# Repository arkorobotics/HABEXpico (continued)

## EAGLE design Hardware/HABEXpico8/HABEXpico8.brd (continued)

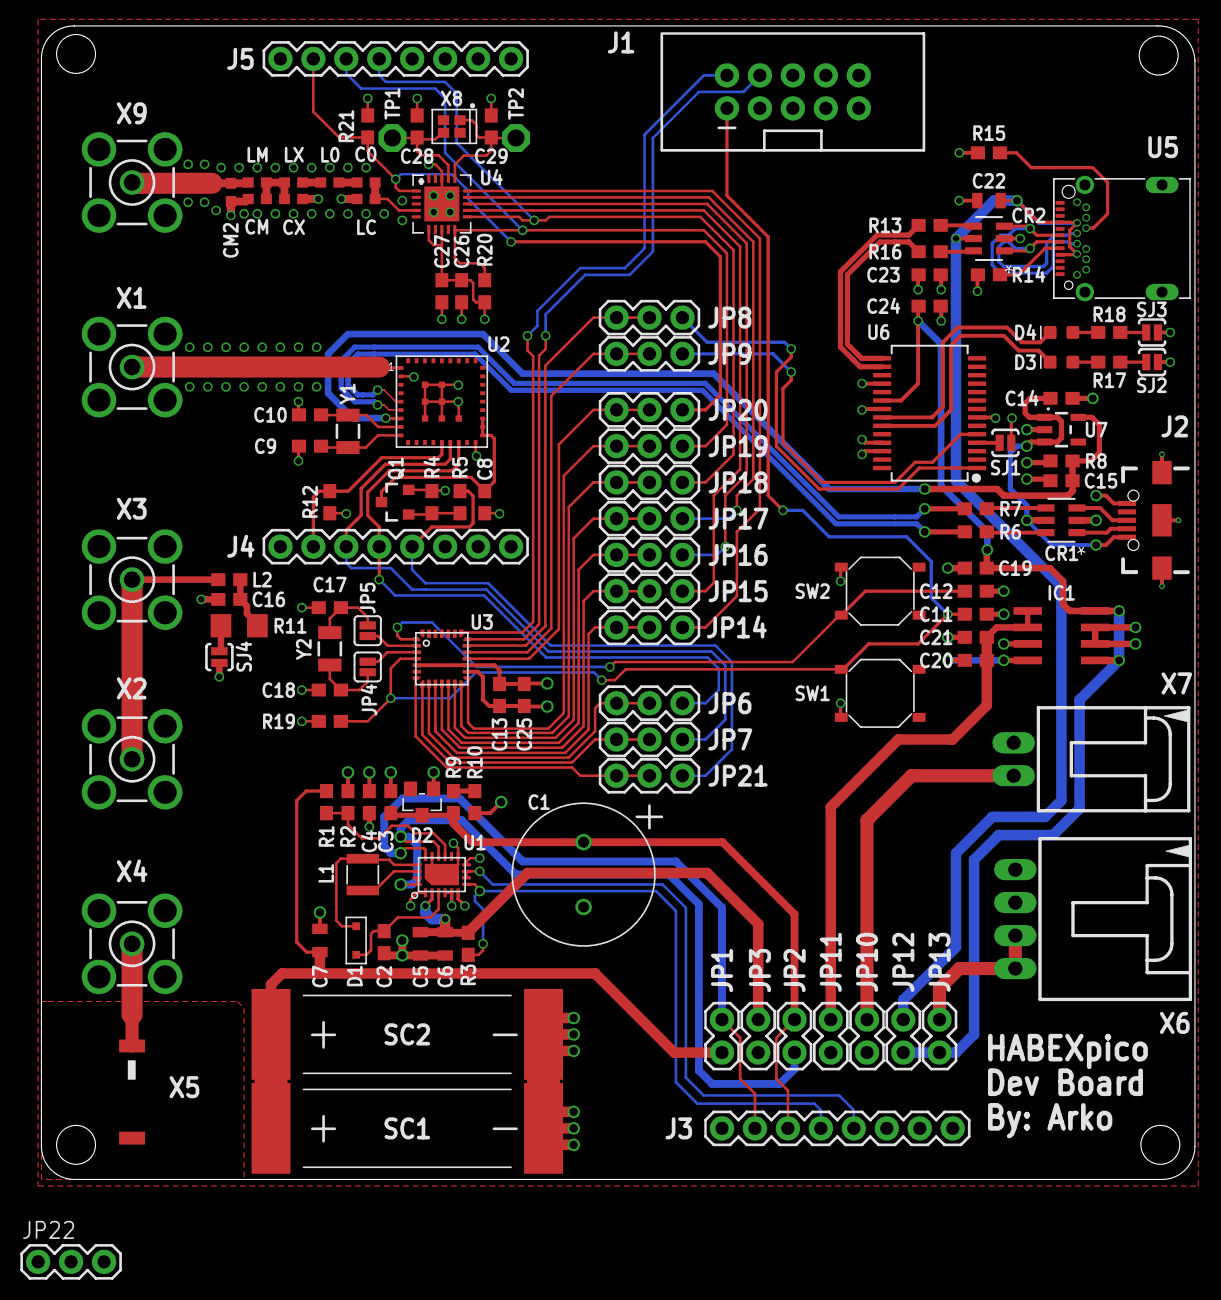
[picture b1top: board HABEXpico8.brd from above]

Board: 4 copper layers, 88.9 x 88.9 mm, 123 parts (0 on the bottom side), 93 nets.

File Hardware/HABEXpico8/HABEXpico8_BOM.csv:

"Qty";"Value";"Device";"Package";"Parts";"Description";"MANUFACTURER_PART_NUMBER";"MF";"MFG_PN";"MPN";"OC_FARNELL";"OC_NEWARK";"PROD_ID";"SF_ID";"SPICEPREFIX";"TP_SIGNAL_NAME";"VALUE";"VENDOR";
"5";"";"BU-SMA-V";"BU-SMA-V";"X1, X2, X3, X4, X9";"FEMALE SMA CONNECTOR";"";"";"";"";"unknown";"unknown";"";"";"";"";"";"";
"1";"";"CONN_05X2SHD";"2X5-SHROUDED";"J1";"Multi connection point. Often used as Generic Header-pin footprint for 0.1 inch spaced/style header connections";"";"";"";"";"";"";"CONN-08671";"PRT-08506";"";"";"";"";
"3";"";"CONN_08"";"1X08";"J3, J4, J5";"Multi connection point. Often used as Generic Header-pin footprint for 0.1 inch spaced/style header connections";"";"";"";"";"";"";"CONN-08438";"";"";"";"";"";
"7";"";"JUMPER-2PTH";"1X02";"JP1, JP2, JP3, JP10, JP11, JP12, JP13";"Jumper";"";"";"";"";"";"";"";"";"";"";"";"";
"12";"";"JUMPER-3PTH";"1X03";"JP6, JP7, JP8, JP9, JP14, JP15, JP16, JP17, JP18, JP19, JP20, JP21";"";"";"";"";"";"";"";"";"";"";"";"";"";
"2";"";"JUMPER-SMT_2_NO_SILK";"SMT-JUMPER_2_NO_SILK";"JP4, JP5";"Normally open jumper";"";"";"";"";"";"";"";"";"";"";"";"";
"1";"";"LT1763CS8-3.3";"SOIC8";"IC1";"500mA, Low Noise, LDO Micropower Regulators";"";"";"";"LT1763CS8-3.3";"1273617";"57M6055";"";"";"";"";"";"";
"1";"";"SLVU2.8HTG";"SOT-23";"D2";"TVS Diode";"";"";"";"";"";"";"";"";"";"";"";"";
"4";"";"SOLDERJUMPERNO";"SJ_2S-NO";"SJ1, SJ2, SJ3, SJ4";"Solder Jumper";"";"";"";"";"";"";"";"";"";"";"";"";
"1";"";"USB_AB_SMT";"USB-AB-MICRO-SMD";"J2";"USB Type AB Micro Connector";"";"";"";"";"";"";"CONN-11794";"";"";"";"";"";
"7";" ";"RESISTOR0603";"0603";"R1, R2, R3, R9, R10, R14, R15";"Generic Resistor Package";"";"";"";"";"";"";" ";"";"";"";" ";"";
"2";"0.1uF";"0.1UF-0603-25V-(+80/-20%)";"0603";"C4, C8";"0.1µF ceramic capacitors";"";"";"";"";"";"";"CAP-00810";"";"";"";"0.1uF";"";
"7";"0.1uF";"0.1UF-0603-25V-5%";"0603";"C11, C12, C13, C16, C23, C24, C27";"0.1µF ceramic capacitors";"";"";"";"";"";"";"CAP-08604";"";"";"";"0.1uF";"";
"3";"1.0uF";"1.0UF-0603-16V-10%";"0603";"C14, C15, C19";"1µF ceramic capacitors";"";"";"";"";"";"";"CAP-00868";"";"";"";"1.0uF";"";
"1";"10";"10OHM-1206-1/4W-1%";"1206";"R11";"10Ω resistor";"";"";"";"";"";"";"RES-08705";"";"";"";"10";"";
"1";"100";"100OHM-0603-1/10W-1%";"0603";"R5";"100Ω resistor";"";"";"";"";"";"";"RES-07863";"";"";"";"100";"";
"3";"100k";"100KOHM-0603-1/10W-1%";"0603";"R8, R20, R21";"100kΩ resistor";"";"";"";"";"";"";"RES-07828";"";"";"";"100k";"";
"3";"10k";"10KOHM-0603-1/10W-1%";"0603";"R4, R12, R19";"10kΩ resistor";"";"";"";"";"";"";"RES-00824";"";"";"";"10k";"";
"2";"10nF";"10NF-0603-50V-10%";"0603";"C20, C26";"0.01uF/10nF/10,000pF ceramic capacitors";"";"";"";"";"";"";"CAP-00867";"";"";"";"10nF";"";
"2";"10pF";"10PF-0603-50V-5%";"0603";"C28, C29";"10pF ceramic capacitors";"";"";"";"";"";"";"CAP-11812";"";"";"";"10pF";"";
"1";"10pF";"CAPACITOR_0603_L";"RESC0603_L";"CX";"Generic chip capacitor";"";"";"";"";"";"";"";"";"";"";"";"";
"2";"10uF";"10UF-0603-6.3V-20%";"0603";"C21, C25";"10.0µF ceramic capacitors";"";"";"";"";"";"";"CAP-11015";"";"";"";"10uF";"";
"1";"10uF";"10UF-0805-10V-10%";"0805";"C22";"10.0µF ceramic capacitors";"";"";"";"";"";"";"CAP-11330";"";"";"";"10uF";"";
"1";"10uH";"INDUCTOR-1210";"1210-INDUCTOR";"L1";"Inductor, 1210 Package";"";"";"";"";"";"";"";"";"";"";"";"";
"1";"12nH";"INDUCTOR_0603_L";"RESC0603_L";"LM";"Generic chip inductor";"";"";"";"";"";"";"";"";"";"";"";"";
"1";"140nH";"INDUCTOR_0603_L";"RESC0603_L";"LX";"Generic chip inductor";"";"";"";"";"";"";"";"";"";"";"";"";
"1";"2.2uF";"2.2UF-0603-10V-20%";"0603";"C2";"2.2µF ceramic capacitors";"";"";"";"";"";"";"CAP-07888";"";"";"";"2.2uF";"";
"1";"2.5A/30V";"MOSFET-PCHANNELDMG2307L";"SOT23-3";"Q1";"Generic PMOSFET";"";"";"";"";"";"";"TRANS-11308";"";"";"";"2.5A/30V";"";
"1";"22pF";"CAPACITOR_0603_L";"RESC0603_L";"C0";"Generic chip capacitor";"";"";"";"";"";"";"";"";"";"";"";"";
"3";"22uF";"22UF-0805-6.3V-20%";"0805";"C5, C6, C7";"22µF ceramic capacitors";"";"";"";"";"";"";"CAP-08402";"";"";"";"22uF";"";
"4";"27";"27OHM-0603-1/10W-1%";"0603";"R6, R7, R13, R16";"27Ω resistor";"";"";"";"";"";"";"RES-09334";"";"";"";"27";"";
"1";"3.3V";"V_REG_AP2112K-3.3V";"SOT23-5";"U7";"AP2112 - 600mA CMOS LDO Regulator w/ Enable";"";"";"";"";"";"";"VREG-12457";"";"";"";"3.3V";"";
"2";"300";"300OHM-0603-1/10W-1%";"0603";"R17, R18";"300Ω resistor";"";"";"";"";"";"";"RES_10328";"";"";"";"300";"";
"1";"30MHZ 402F3001XIAR";"CRYSTALS-GND-LID-IQXC-42";"2.0X1.6-4-PAD";"X8";"CRYSTALS WITH CAN GROUNDED";"";"";"";"";"";"";"";"";"";"";"";"";
"2";"32.768kHz";"CRYSTAL-32.768KHZSMD-3.2X1.5";"CRYSTAL-SMD-3.2X1.5MM";"Y1, Y2";"32.768kHz Crystal";"";"";"";"";"";"";"XTAL-13062";"";"";"";"32.768kHz";"";
"1";"33nH/±5%/500mA";"INDUCTOR-0603-33NH";"0603";"L2";"Inductors";"";"";"";"";"";"";"NDUC-07874";"";"";"";"33nH/±5%/500mA";"";
"1";"4.7pF";"CAPACITOR_0603_L";"RESC0603_L";"CM";"Generic chip capacitor";"";"";"";"";"";"";"";"";"";"";"";"";
"1";"4.7uF";"4.7UF0603";"0603";"C3";"4.7µF ceramic capacitors";"";"";"";"";"";"";"CAP-08280";"";"";"";"4.7uF";"";
"1";"470nH";"INDUCTOR_0603_L";"RESC0603_L";"LC";"Generic chip inductor";"";"";"";"";"";"";"";"";"";"";"";"";
"1";"56nH";"INDUCTOR_0603_L";"RESC0603_L";"L0";"Generic chip inductor";"";"";"";"";"";"";"";"";"";"";"";"";
"4";"6pF";"C-EUC0603";"C0603";"C9, C10, C17, C18";"CAPACITOR, European symbol";"";"";"";"";"";"";"";"";"C";"";"";"";
"1";"7.5pF";"CAPACITOR_0603_L";"RESC0603_L";"CM2";"Generic chip capacitor";"";"";"";"";"";"";"";"";"";"";"";"";
"1";"C-GRID-02-70553";"C-GRID-02-70553";"70553-02";"X7";"CONNECTOR";"";"MOLEX";"";"";"unknown";"unknown";"";"";"";"";"";"";
"1";"C-GRID-04-70553";"C-GRID-04-70553";"70553-04";"X6";"CONNECTOR";"";"MOLEX";"";"";"unknown";"unknown";"";"";"";"";"";"";
"1";"EVA-8M";"EVA-8M";"EVA-8M";"U2";"u-blox EVA GNSS module";"";"";"";"";"";"";"";"";"";"";"";"";
"1";"FT232RL";"FT232RLSSOP";"SSOP28DB";"U6";"FT232RL USB UART";"";"";"";"";"";"";"IC-00870";"";"";"";"FT232RL";"";
"1";"GREEN";"LED-GREEN0603";"LED-0603";"D4";"Green SMD LED";"";"";"";"";"";"";"DIO-00821";"";"";"";"GREEN";"";
"1";"JTI_ANTENNA-1575AT43A40";"JTI_ANTENNA-1575AT43A40";"JTI_ANTENNA-1575AT43A40";"X5";"GPS Antenna - SMD";"";"";"";"";"";"";"";"";"";"";"";"";
"2";"KXOB22-04X3";"KXOB22-04X3";"KX0B22";"SC1, SC2";"IXYS Solar Cell";"";"";"";"";"";"";"";"";"";"";"";"";
"1";"LTC3106";"LTC3106";"UDC20QFN";"U1";"LTC Series";"";"";"";"";"";"";"";"";"";"";"";"";
"1";"RED";"LED-RED0603";"LED-0603";"D3";"Red SMD LED";"";"";"";"";"";"";"DIO-00819";"";"";"";"RED";"";
"1";"SI4464";"SI4464";"QFN20+GNDPAD";"U4";"SI Labs";"";"";"";"";"";"";"";"";"";"";"";"";
"2";"SKQGADE010";"SMD-BUTTON(4P-5.2X5.2X1.5MM-SKQGADE010)-SKQGADE010";"SW4-SMD-5.2X5.2X1.5MM";"SW1, SW2";"311020017";"";"";"";"SKQGADE010";"";"";"";"";"";"";"SKQGADE010";"";
"1";"STM32L011G4";"STM32L011G4";"UFQFPN28";"U3";"STM32L0 Series";"";"";"";"";"";"";"";"";"";"";"";"";
"2";"TPPAD1-13";"TPPAD1-13";"P1-13";"TP1, TP2";"Test pad";"";"";"";"";"";"";"";"";"";"";"";"";
"1";"TV1030-3R0106-R";"TV1030-3R0106-R";"5.0MM-SUPERCAP";"C1";"10F Supercapacitor";"";"";"";"";"";"";"";"";"";"";"";"";
"1";"USB-C_R/A_HYBRID_RCPT";"USB-C_R/A_HYBRID";"USB-C_R/A_HYBRID_RCPT";"U5";"USB-C Right Angle Hybrid Receptacle";"";"";"12401548E4#2A";"";"";"";"";"";"";"";"";"";
"2";"USBLC6-2SC6";"USBLC6-2SC6";"SOT23-6L";"CR1, CR2";"";"USBLC62SC6";"";"";"";"";"";"";"";"";"";"";"ST Microelectronics";
"1";"ZLLS400";"ZLLS400";"SOD-323";"D1";"SCHOTTKY DIODE, ZLLS400";"";"";"";"";"";"";"";"";"";"";"";"";

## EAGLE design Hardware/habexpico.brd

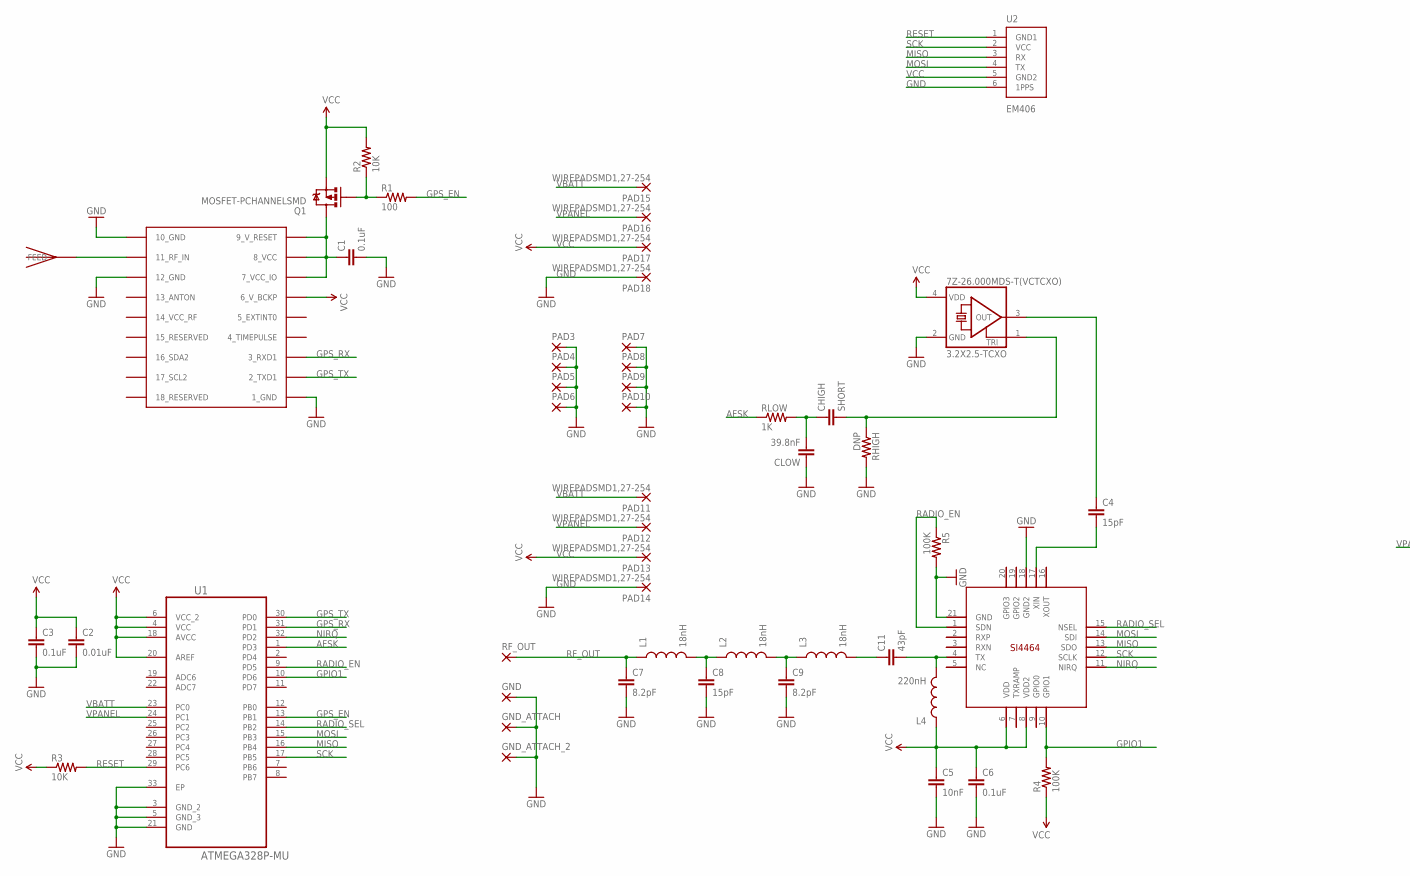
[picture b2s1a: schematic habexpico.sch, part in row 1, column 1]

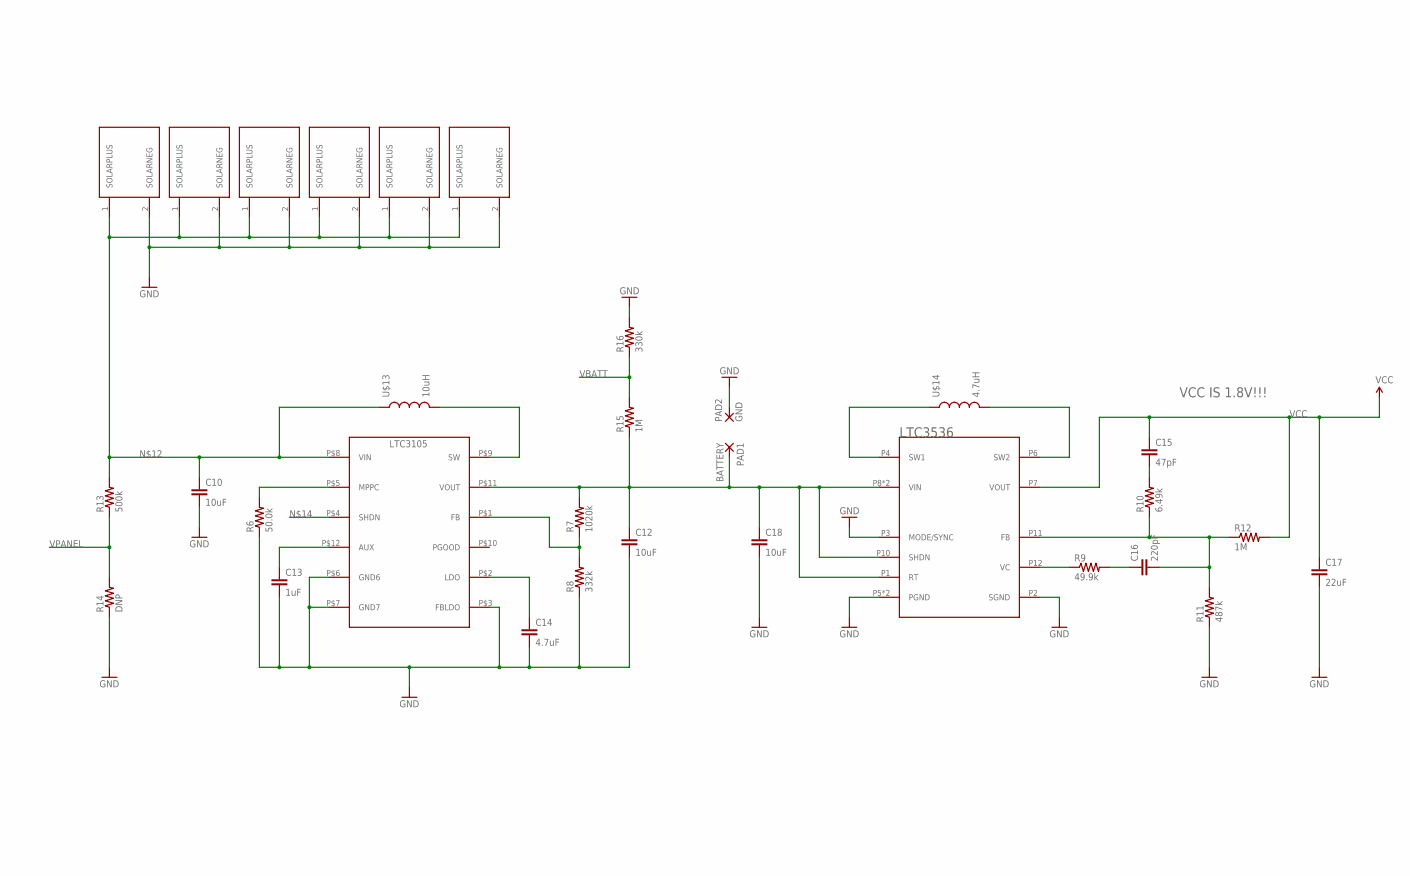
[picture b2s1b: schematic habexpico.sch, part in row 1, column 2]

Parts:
7Z-26.000MDS-T(VCTCXO): 3.2X2.5-TCXO
C1, C3, C6: 0.1uF; 0603-CAP
C2: 0.01uF; 0603-CAP
C4, C8: 15pF; 0603-CAP
C5: 10nF; 0603-CAP
C7, C9: 8.2pF; 0603-CAP
C10, C12, C18: 10uF; 0805
C11: 43pF; 0603-CAP
C13: 1uF; 0603-CAP
C14: 4.7uF; 0603-CAP
C15: 47pF; 0603-CAP
C16: 220pF; 0603-CAP
C17: 22uF; 0603-CAP
CHIGH: SHORT; 0603-CAP
CLOW: 39.8nF; 0603-CAP
GND: SMD5; SMD2,54-5,08
GND_ATTACH: SMD2; SMD1,27-2,54
GND_ATTACH_2: SMD2; SMD1,27-2,54
L1, L2, L3: 18nH; 0603
L4: 220nH; 0603
PAD1: BATTERY; 5-2,5
PAD2: GND; 5-2,5
PAD3, PAD4, PAD5, PAD6, PAD7, PAD8, PAD9, PAD10: SMD2; SMD1,27-2,54
PAD11, PAD12, PAD13, PAD14, PAD15, PAD16, PAD17, PAD18: WIREPADSMD1,27-254; SMD1,27-2,54
Q1: MOSFET-PCHANNELSMD; SOT23-3
R1: 100; 0603-RES
R2, R3: 10K; 0603-RES
R4, R5: 100K; 0603-RES
R6: 50.0k; 0603-RES
R7: 1020k; 0603-RES
R8: 332k; 0603-RES
R9: 49.9k; 0603-RES
R10: 6.49k; 0603-RES
R11: 487k; 0603-RES
R12, R15: 1M; 0603-RES
R13: 500k; 0603-RES
R14: DNP; 0603-RES
R16: 330k; 0603-RES
RF_OUT: SMD5; SMD2,54-5,08
RHIGH: DNP; 0603-RES
RLOW: 1K; 0603-RES
U1: ATMEGA328P-MU; QFN50P500X500X100-33N
U2: EM406
U$1: SI4464; QFN20+GNDPAD
U$2: UBLOX_MAX
U$4: JTI_ANTENNA-1575AT43A40
U$5: LTC3105
U$6: LTC3536; LTC3536-MSE
U$7, U$8, U$9, U$10, U$11, U$12: KXOB22-12X1
U$13: 10uH; COILCRAFT_MSS5131
U$14: 4.7uH; COILCRAFT_MSS5131

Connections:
AFSK: RLOW.1, U1.1 (PD3)
GND: 7Z-26.000MDS-T(VCTCXO).2 (GND), C1.2, C2.2, C3.2, C5.2, C6.2, C7.2, C8.2, C9.2, C10.2, C12.2, C13.2, C14.2, C17.2, C18.2, CLOW.1, GND.1, GND_ATTACH.1, GND_ATTACH_2.1, PAD2.1, PAD3.1, PAD4.1, PAD5.1, PAD6.1, PAD7.1, PAD8.1, PAD9.1, PAD10.1, PAD14.1, PAD18.1, R5.2, R6.1, R8.1, R11.1, R14.1, R16.2, RHIGH.2, U1.3 (GND_2), U1.5 (GND_3), U1.21 (GND), U1.33 (EP), U2.6 (1PPS), U$1.18 (GND2), U$1.21 (GND), U$2.1_GND, U$2.10_GND, U$2.12_GND, U$5.P$3 (FBLDO), U$5.P$6 (GND6), U$5.P$7 (GND7), U$6.P2 (SGND), U$6.P3 (MODE/SYNC), U$6.P5 (PGND), U$6.P13 (PGND), U$7.2 (SOLARNEG), U$8.2 (SOLARNEG), U$9.2 (SOLARNEG), U$10.2 (SOLARNEG), U$11.2 (SOLARNEG), U$12.2 (SOLARNEG)
GPIO1: R4.2, U1.10 (PD6), U$1.10 (GPIO1)
GPS_EN: R1.2, U1.13 (PB1)
GPS_RX: U1.31 (PD1), U$2.3_RXD1
GPS_TX: U1.30 (PD0), U$2.2_TXD1
MISO: U1.16 (PB4), U2.3 (RX), U$1.13 (SDO)
MOSI: U1.15 (PB3), U2.4 (TX), U$1.14 (SDI)
unnamed: U$2.11_RF_IN, U$4.FEED
unnamed: C1.1, Q1.3 (D), U$2.7_VCC_IO, U$2.8_VCC, U$2.9_V_RESET
unnamed: Q1.1 (G), R1.1, R2.1
unnamed: C11.2, L4.2, U$1.4 (TX)
unnamed: C11.1, L3.2
unnamed: 7Z-26.000MDS-T(VCTCXO).3 (OUT), C4.1
unnamed: C4.2, U$1.17 (XIN)
unnamed: C9.1, L2.2, L3.1
unnamed: C8.1, L1.2, L2.1
unnamed: R6.2, U$5.P$5 (MPPC)
unnamed: C10.1, R13.2, U$5.P$8 (VIN), U$7.1 (SOLARPLUS), U$8.1 (SOLARPLUS), U$9.1 (SOLARPLUS), U$10.1 (SOLARPLUS), U$11.1 (SOLARPLUS), U$12.1 (SOLARPLUS), U$13.P$2 (1)
unnamed: U$5.P$9 (SW), U$13.P$1 (2)
unnamed: C13.1, U$5.P$12 (AUX)
unnamed: C14.1, U$5.P$2 (LDO)
unnamed: CHIGH.1, CLOW.2, RLOW.2
unnamed: R7.1, R8.2, U$5.P$1 (FB)
unnamed: C12.1, C18.1, PAD1.1, R7.2, R15.1, U$5.P$11 (VOUT), U$6.P1 (RT), U$6.P8 (VIN), U$6.P9 (VIN), U$6.P10 (SHDN)
unnamed: 7Z-26.000MDS-T(VCTCXO).1 (TRI), CHIGH.2, RHIGH.1
unnamed: U$6.P4 (SW1), U$14.P$2 (1)
unnamed: U$6.P6 (SW2), U$14.P$1 (2)
unnamed: C15.2, R10.2
unnamed: C16.2, R10.1, R11.2, R12.1, U$6.P11 (FB)
unnamed: C16.1, R9.2
unnamed: R9.1, U$6.P12 (VC)
NIRQ: U1.32 (PD2), U$1.11 (NIRQ)
RADIO_EN: R5.1, U1.9 (PD5), U$1.1 (SDN)
RADIO_SEL: U1.14 (PB2), U$1.15 (NSEL)
RESET: R3.2, U1.29 (PC6), U2.1 (GND1)
RF_OUT: C7.1, L1.1, RF_OUT.1
SCK: U1.17 (PB5), U2.2 (VCC), U$1.12 (SCLK)
VBATT: PAD11.1, PAD15.1, R15.2, R16.1, U1.23 (PC0)
VCC: 7Z-26.000MDS-T(VCTCXO).4 (VDD), C2.1, C3.1, C5.1, C6.1, C15.1, C17.1, L4.1, PAD13.1, PAD17.1, Q1.2 (S), R2.2, R3.1, R4.1, R12.2, U1.4 (VCC), U1.6 (VCC_2), U1.18 (AVCC), U1.20 (AREF), U2.5 (GND2), U$1.6 (VDD), U$1.8 (VDD2), U$2.6_V_BCKP, U$6.P7 (VOUT)
VPANEL: PAD12.1, PAD16.1, R13.1, R14.2, U1.24 (PC1)

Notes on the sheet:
VCC IS 1.8V!!!

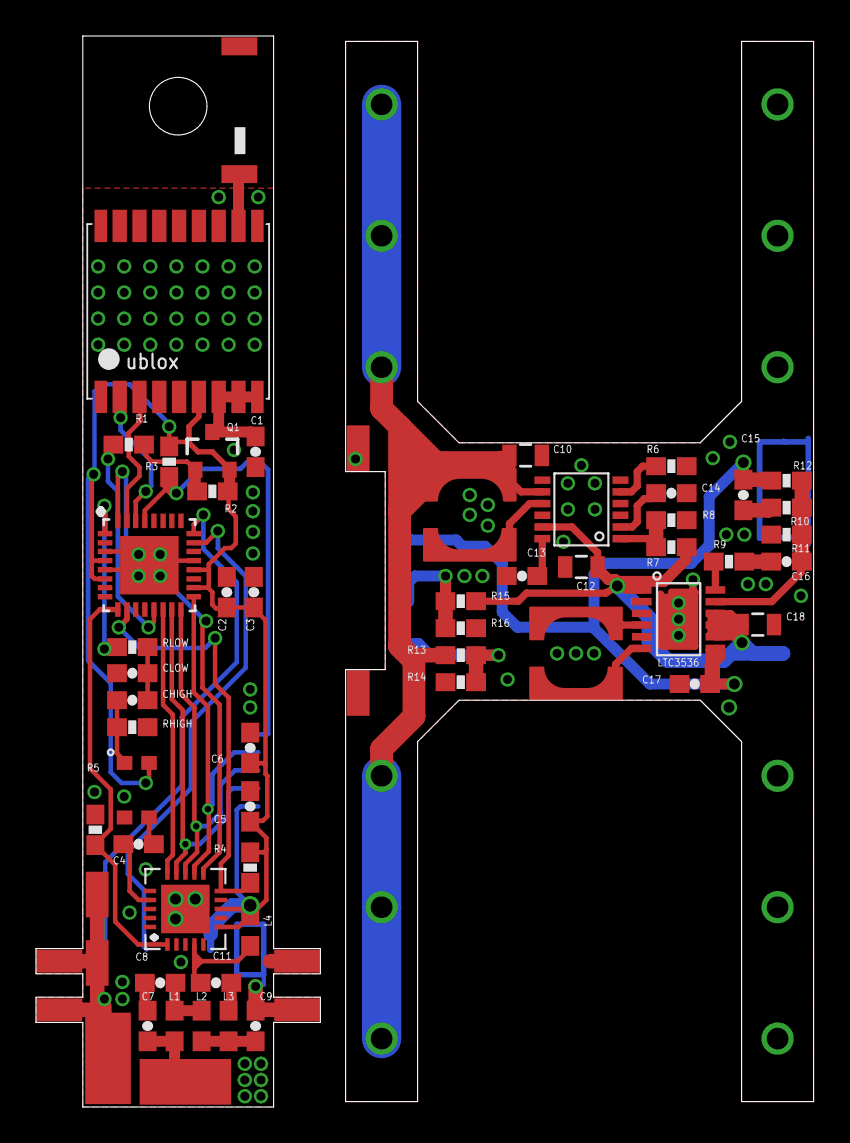
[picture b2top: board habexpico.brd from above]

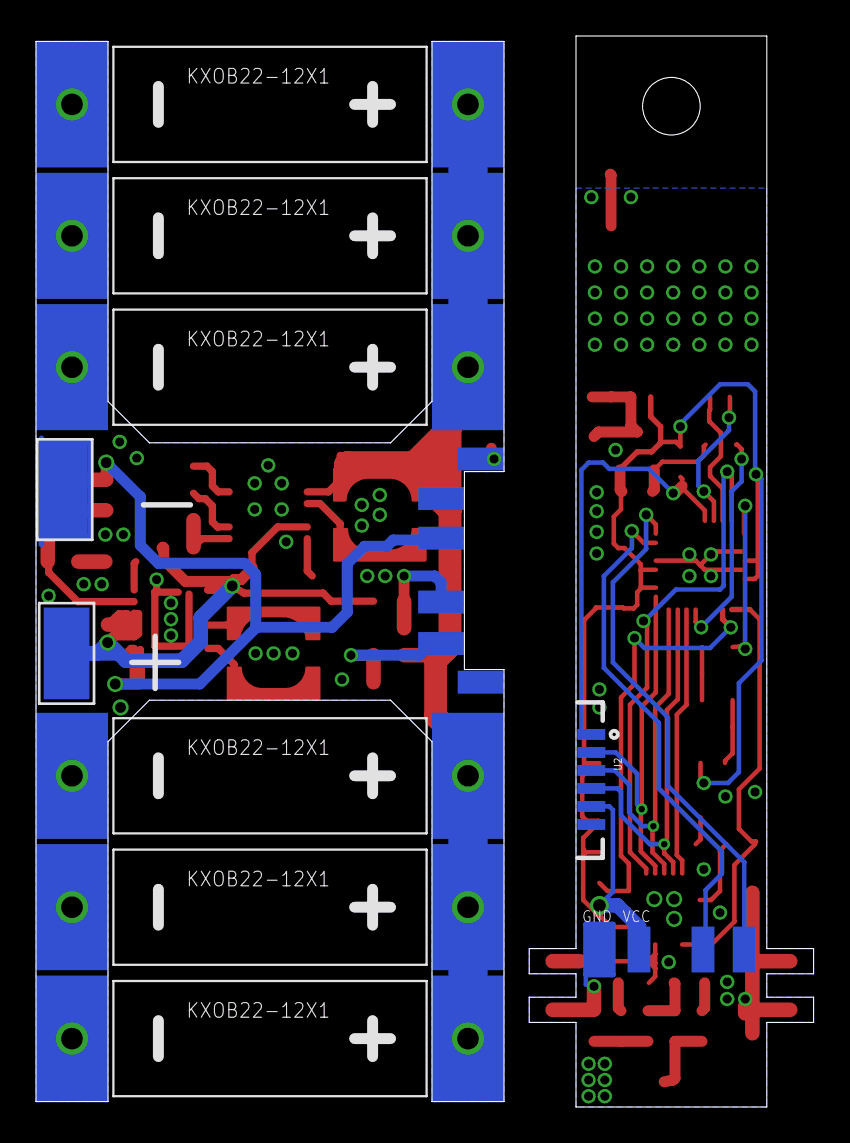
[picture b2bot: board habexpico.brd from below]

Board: 2 copper layers, 43.2 x 59.5 mm, 81 parts (19 on the bottom side), 41 nets.

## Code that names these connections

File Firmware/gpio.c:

#include "main.h"
#include "gpio.h"

// PORT B
gpio BO = {.net = PB0, .ddr = &DDRB, .port = &PORTB, .pin = &PINB};
gpio B1 = {.net = PB1, .ddr = &DDRB, .port = &PORTB, .pin = &PINB};
gpio B2 = {.net = PB2, .ddr = &DDRB, .port = &PORTB, .pin = &PINB};
gpio B3 = {.net = PB3, .ddr = &DDRB, .port = &PORTB, .pin = &PINB};
gpio B4 = {.net = PB4, .ddr = &DDRB, .port = &PORTB, .pin = &PINB};
gpio B5 = {.net = PB5, .ddr = &DDRB, .port = &PORTB, .pin = &PINB};
gpio B6 = {.net = PB6, .ddr = &DDRB, .port = &PORTB, .pin = &PINB};
gpio B7 = {.net = PB7, .ddr = &DDRB, .port = &PORTB, .pin = &PINB};

// PORT C
gpio CO = {.net = PC0, .ddr = &DDRC, .port = &PORTC, .pin = &PINC};
gpio C1 = {.net = PC1, .ddr = &DDRC, .port = &PORTC, .pin = &PINC};
gpio C2 = {.net = PC2, .ddr = &DDRC, .port = &PORTC, .pin = &PINC};
gpio C3 = {.net = PC3, .ddr = &DDRC, .port = &PORTC, .pin = &PINC};
gpio C4 = {.net = PC4, .ddr = &DDRC, .port = &PORTC, .pin = &PINC};
gpio C5 = {.net = PC5, .ddr = &DDRC, .port = &PORTC, .pin = &PINC};
gpio C6 = {.net = PC6, .ddr = &DDRC, .port = &PORTC, .pin = &PINC};

// PORT D
gpio DO = {.net = PD0, .ddr = &DDRD, .port = &PORTD, .pin = &PIND};
gpio D1 = {.net = PD1, .ddr = &DDRD, .port = &PORTD, .pin = &PIND};
gpio D2 = {.net = PD2, .ddr = &DDRD, .port = &PORTD, .pin = &PIND};
gpio D3 = {.net = PD3, .ddr = &DDRD, .port = &PORTD, .pin = &PIND};
gpio D4 = {.net = PD4, .ddr = &DDRD, .port = &PORTD, .pin = &PIND};
gpio D5 = {.net = PD5, .ddr = &DDRD, .port = &PORTD, .pin = &PIND};
gpio D6 = {.net = PD6, .ddr = &DDRD, .port = &PORTD, .pin = &PIND};
gpio D7 = {.net = PD7, .ddr = &DDRD, .port = &PORTD, .pin = &PIND};

void gpio_pin_mode(gpio pin, uint8_t mode)
{
	*pin.ddr =  mode ? (*pin.ddr | (1 << pin.net)) : (*pin.ddr & ~(1 << pin.net));
}

void gpio_pin_state(gpio pin, uint8_t state)
{
	// Needs to be revised
	//*pin.pin =  state ? (*pin.pin | (1 << pin.net)) : (*pin.pin & ~(1 << pin.net));
}

void gpio_pin_set(gpio pin, uint8_t level)
{
	*pin.port =  level ? (*pin.port | (1 << pin.net)) : (*pin.port & ~(1 << pin.net));
}

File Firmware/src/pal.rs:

// Peripheral Abstraction Layer

use stm32l0xx_hal::{pac, prelude::*, rcc::Config, adc, gpio, serial, spi, timer::*};

pub struct PAL {
    pub console_tx: serial::Tx<serial::USART2>,                     // Console TX
    pub console_rx: serial::Rx<serial::USART2>,                     // Console RX
    pub gps_tx: serial::Tx<serial::LPUART1>,                        // GPS TX
    pub gps_rx: serial::Rx<serial::LPUART1>,                        // GPS RX
    pub gps_en: gpio::gpioa::PA1<gpio::Output<gpio::PushPull>>,     // GPS Enable Pin
    pub radio_spi: spi::Spi< pac::SPI1, (gpio::gpioa::PA5<gpio::Analog>, // Radio SPI
                                        gpio::gpioa::PA6<gpio::Analog>, 
                                        gpio::gpioa::PA7<gpio::Analog>)>,   
    pub radio_nss: gpio::gpioa::PA4<gpio::Output<gpio::PushPull>>,  // Radio Chip Select Pin
    pub adc: adc::Adc<adc::Ready>,                                    // Analog To Digital Converter
    pub adc_vstore: gpio::gpioa::PA0<gpio::Analog>,                 // Storage Voltage
    pub timer: Timer<pac::TIM2>,
}

impl PAL {
    pub fn new() -> Self {
        // Create Peripheral Struct
        let dp = pac::Peripherals::take().unwrap();

        // Configure the clock
        let mut rcc = dp.RCC.freeze(Config::hsi16());

        // Acquire the GPIOA peripheral
        let gpioa = dp.GPIOA.split(&mut rcc);

        // Configure Debug Serial Pins
        let debug_tx_pin = gpioa.pa9;
        let debug_rx_pin = gpioa.pa10;

        // //Configure the debug serial peripheral
        let debug_serial = dp
            .USART2
            .usart(debug_tx_pin, debug_rx_pin, 
                serial::Config {
                    baudrate: 115_200_u32.bps(),
                    wordlength: serial::WordLength::DataBits8,
                    parity: serial::Parity::ParityNone,
                    stopbits: serial::StopBits::STOP1,
                }, 
                &mut rcc)
            .unwrap();

        let (console_tx, console_rx) = debug_serial.split();
        
        // Configure GPS
        let gps_en = gpioa.pa1.into_push_pull_output();

        // Configure GPS Serial Pins
        let gps_tx_pin = gpioa.pa2;
        let gps_rx_pin = gpioa.pa3;

        // Configure the GPS serial peripheral
        let gps_serial = dp
            .LPUART1
            .usart(gps_tx_pin, gps_rx_pin, 
                serial::Config {
                    baudrate: 9_600_u32.bps(),
                    wordlength: serial::WordLength::DataBits8,
                    parity: serial::Parity::ParityNone,
                    stopbits: serial::StopBits::STOP1,
                },
                &mut rcc)
            .unwrap();

        let (gps_tx, gps_rx) = gps_serial.split();

        // Initialize SPI
        let radio_nss = gpioa.pa4.into_push_pull_output();
        let sck = gpioa.pa5;
        let miso = gpioa.pa6;
        let mosi = gpioa.pa7;

        // Initialise the SPI peripheral.
        let radio_spi = dp
            .SPI1
            .spi((sck, miso, mosi), spi::MODE_0, 100_000.hz(), &mut rcc);

        
        // Configure ADC
        let adc = dp.ADC.constrain(&mut rcc);

        // Configure PA0 as analog.
        let adc_vstore = gpioa.pa0.into_analog();

        // Configure the timer.
        let timer = dp.TIM2.timer(1.hz(), &mut rcc);

        return PAL {
            console_tx: console_tx,
            console_rx: console_rx,
            gps_tx: gps_tx,
            gps_rx: gps_rx,
            gps_en: gps_en,
            radio_spi: radio_spi,
            radio_nss: radio_nss,
            adc: adc,
            adc_vstore: adc_vstore,
            timer: timer
        }
    }
}

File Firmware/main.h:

#ifndef MAIN_H
#define MAIN_H

#include <inttypes.h>
#include <avr/io.h>
#include <avr/interrupt.h>
#include <avr/sleep.h>
#include <util/delay.h>
#include <stdint.h>

#define FOSC       	1000000UL
#define UART0_BAUD 	9600UL
#define I2C_FREQ 	100000UL

// PIN DEFINITIONS
#define GPS_EN		B1
#define RADIO_SS	B2
#define MOSI	 	PB3
#define MISO	 	PB4
#define SCK		  	PB5

#define VBATT 		CO
#define VPANEL 		C1

#define GPS_TX 		D0
#define GPS_RX 		D1
#define NIRQ 		D2
#define AFSK 		D3
#define RADIO_EN 	D5
#define GPIO1 		D6

#define LED 		B5

int main(void);

#endif

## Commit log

2017-07-15 Added PCB and schematic
2017-07-15 remove lock files
2017-08-19 Initial codebase commit, includes main and basic peripheral libraries
2017-10-15 Complete Redesign
    ATMega328 did not provide sufficient debug capabilities. Scrapped the
    previous design and restarted using STM32L011. Added new mass and power
    budget report.
2017-10-15 Updated schematic design
    Power save support ICs, updated power budget
2017-10-19 Finished GPS and Power System schematic
    Finished GPS and Power System schematic, minor tweaks may follow.
2017-10-24 Updated Power System, detailed GPS and MCU
    Updated Power System, detailed GPS and MCU, removed backup files.
2017-11-01 Added RF Front End w/ Simulation
    Added RF Front End w/ Simulation
2017-11-06 Finished schematic and simulations
    Finished schematic and simulations. Expecting to make small tweaks in
    future revisions.
2018-08-26 Added BOM, updated board/schematic files
    Added BOM, updated board/schematic files
2018-12-16 The commit before I broke everything
    The commit before I broke everything
2018-12-19 Starting from scratch
    Starting from scratch
2018-12-20 Initial commit of revised rust firmware
    Initial commit of revised rust firmware
2018-12-20 Added build folder to gitignore
    Added build folder to gitignore
2019-06-05 Updated project to use the new stm32l0xx-hal
    Updated project to use the new stm32l0xx-hal
2019-06-16 Echo GPS serial data out debug console
    Echo GPS serial data out debug console
2019-07-05 Updated debugging tools
    Updated debugging tools
2019-07-07 Changed stm32l0xx-hal dependencies to point to local copy
    Changed stm32l0xx-hal dependencies to point to local copy for development. This will be changed back once most of the bugs with stm32l0xx-hal are resolved.
2019-07-07 Switched to debug build
    Switched to debug build
2019-07-07 Working serial printing and GPS echo
    Working serial printing and GPS echo
2019-07-08 Added UART bootloader programming support
    Added UART bootloader programming support
2019-11-30 Starting over again with the multi-file split
2019-11-30 Updated cargo to use latest hal
2019-12-01 Initial gps module. This is meant to be a proof of concept for reference. Big changes coming soon
2019-12-03 First mockup of the peripheral abstraction layer based HABEXpico code base
2019-12-03 Working multi-file version of the habexpico peripheral demo
2019-12-03 Upgraded to hal dependency to v0.5.0
2019-12-04 Added timer. It compiles but doesn't work. Suspect that it's a scope and or lifetime issue. Gonna move this to main
2019-12-04 failing to build with move error
2019-12-04 Compiles but crashes at the first timer interrupt (@1second)
2019-12-04 Timer 21 behaves the same and Timer 3 seems to never call the interrupt. Going to try the debugger next. Maybe running out of ram?
2019-12-05 Shit starting working overnight for no easily understanable reason. Metastable systems are the bane of my existence. With a few tweaks, the time keeper is usable now
2019-12-05 Cleaned up a tad
2019-12-05 Cleaner and better timekeeping
2019-12-16 Removed fmt because it was taking up far too much flash. Resorting to byte array storage and decoding... yay
2019-12-22 Given the incredibly small size constraints for this project, it makes more sense to make nfmt and use fixed sizes than to use fmt
2019-12-23 Very primative version nfmt. More capabilities to come...
2019-12-23 Working nfmt u32-to-string function plus demo code
2020-05-05 Updated codebase to stm32l0xx-hal v0.6.2
    Updated codebase to stm32l0xx-hal v0.6.2
2020-05-18 Resolved two major issues which have plauged the project for ages
    Issue 1: Programming with the ./flash.sh script leads to meta-stable results. Solution: Recommend using the gbd flashing method instead.
    Issue 2: Program crashes after the first NEMA parse. Solution: Clear the UART error bits prior to receiving/parsing GPS data.
2020-05-23 Updated readme and added VSCode support
2020-07-26 Added debug loopback
    Added debug loopback
2020-07-26 Added FT data 200726
    Added FT data 200726
2020-07-27 Added a test script template to start writing/testing the NMEA parser
    Added a test script template to start writing/testing the NMEA parser
2020-09-08 Started gps nmea parser test script
    Started gps nmea parser test script
2020-11-15 Updated nanoformat and added a text script
    Updated nanoformat and added a text script
2020-11-15 Fixed the "-2147483648" print bug
    Fixed the "-2147483648" print bug
2020-11-16 Added ns_to_i32 and h2_to_u8
    Added ns_to_i32 and h2_to_u8. These are needed for parsing NMEA strings in the future.
2020-11-20 Moved test scripts into a single cargo with config
    Moved test scripts into a single cargo with config
2020-11-23 Functional NMEA Parsing. More testing required.
    Functional NMEA Parsing. More testing required.
2020-11-23 Cleaned up some of the checksum code
    Cleaned up some of the checksum code
2020-11-23 Added error handling to nmea, nfmt, and the respective test scripts
    Added error handling to nmea, nfmt, and the respective test scripts
2020-11-24 Added stress test cases and updated todo's in readme
    Added stress test cases and updated todo's in readme
2020-11-24 Added NMEA stress test error checking and resolved all warnings
    Added NMEA stress test error checking and resolved all warnings
2020-11-24 Minor tweaks to readme files
    Minor tweaks to readme files
2020-11-24 Added travis CI
    Added travis CI
2020-11-24 Fixed travis ci file name
    Fixed travis ci file name
2020-11-24 Disabled linker script to possibly solve travis ci build issue
    Disabled linker script to possibly solve travis ci build issue
2020-11-24 More mods to the travis ci
    More mods to the travis ci
2020-11-24 Changed env
    Changed env
2020-11-24 Added installing arm gcc to travis
    Added installing arm gcc to travis
2020-11-24 Disabled linker
    Disabled linker
2020-11-24 Cleaned up a few minor documentation items
    Cleaned up a few minor documentation items
2020-11-24 Added installing cargo bloat
    Added installing cargo bloat
2020-11-24 Basic gps->nmea->return flow. Data valid to follow.
    Basic gps->nmea->return flow. Data valid to follow.
2020-11-24 Hardcoded OpenOCD paths because v0.10.0 *STILL* has the bug where it can't flash/debug the STM32L0
    Hardcoded OpenOCD paths because v0.10.0 *STILL* has the bug where it can't flash/debug the STM32L0
2020-11-25 Fixed GPS UART RX Panic, Updated Console Baud to 115200, and added printing ST
    Fixed GPS UART RX Panic, Updated Console Baud to 115200, and added printing ST
2020-11-25 Fixed ST rollover bug
    Fixed ST rollover bug. System would only hit bug this after 68 years of continious operation, but alas... we can always feel optimistic.
2020-11-27 Found the real bug with the GPS lag... packet fields weren't being cleared prior to searching for $ again
    Found the real bug with the GPS lag... packet fields weren't being cleared prior to searching for $ again
